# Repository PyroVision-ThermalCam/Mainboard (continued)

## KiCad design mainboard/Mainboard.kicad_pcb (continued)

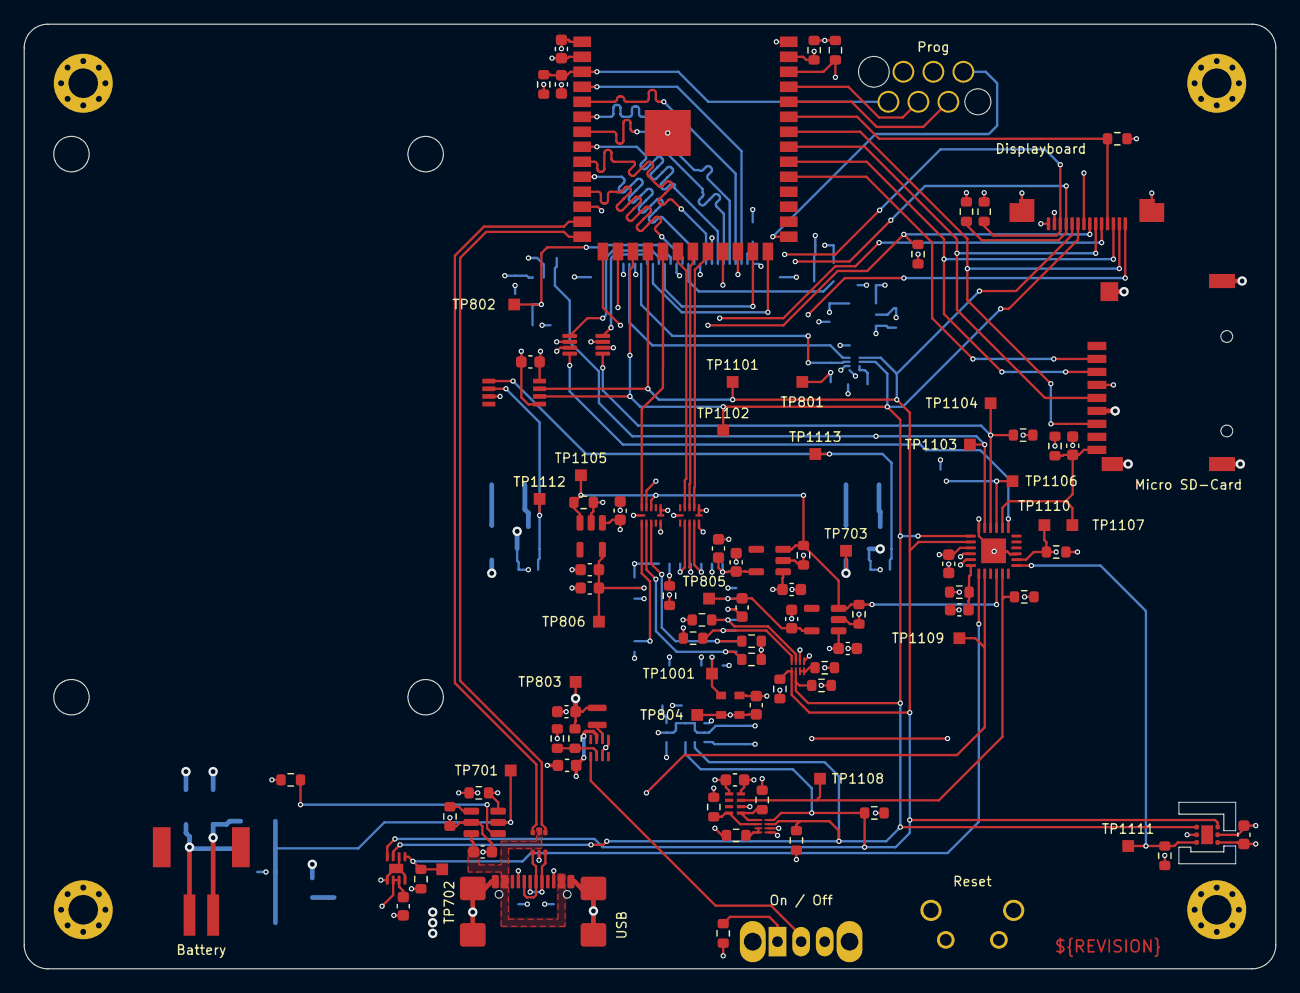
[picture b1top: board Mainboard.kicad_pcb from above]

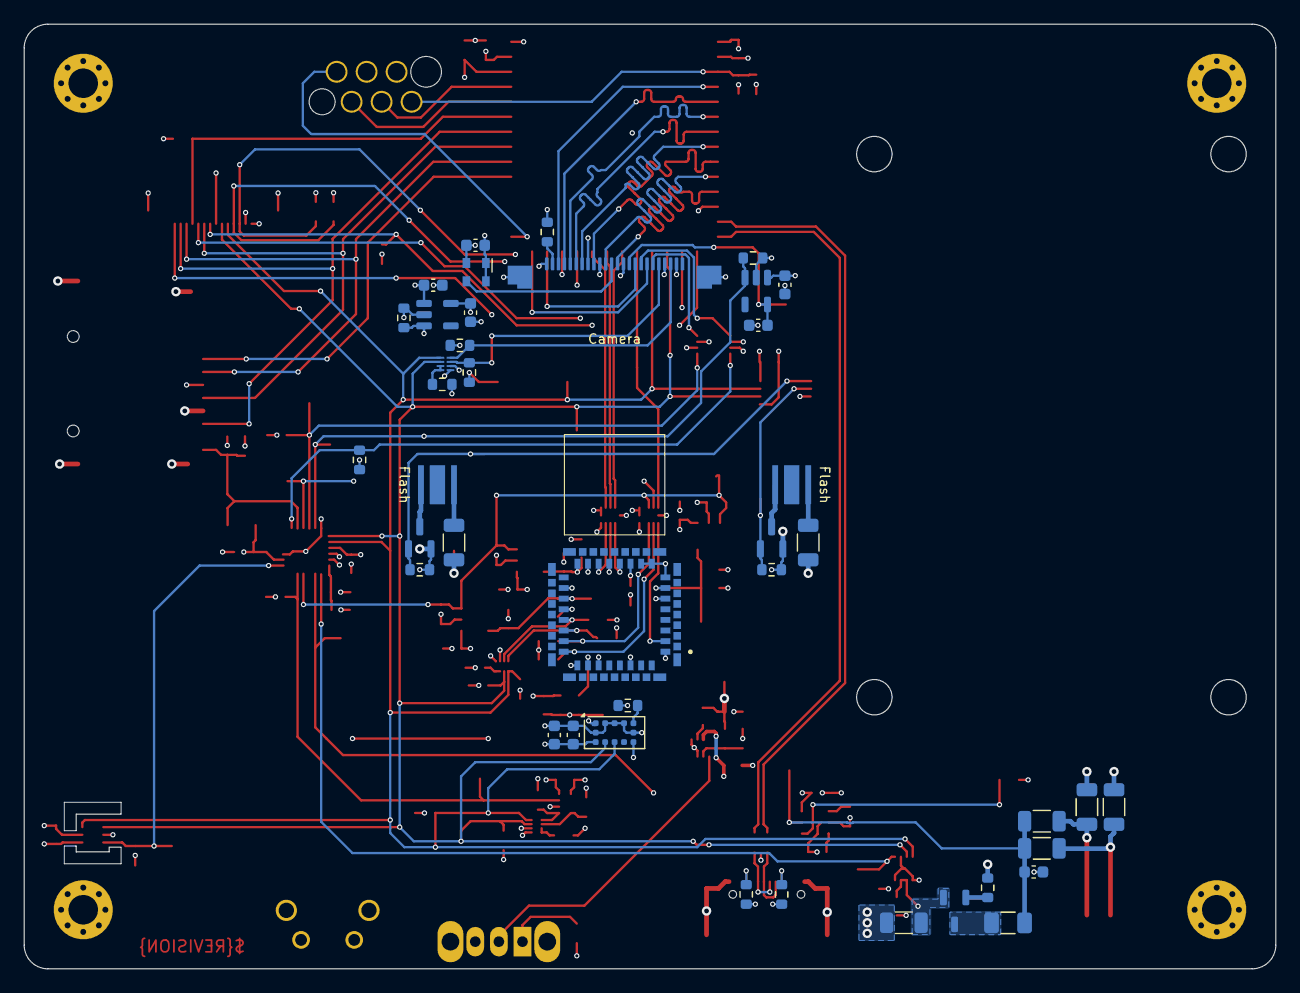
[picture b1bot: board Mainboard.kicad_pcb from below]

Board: 4 copper layers, 106.0 x 80.0 mm, 148 parts (41 on the bottom side), 100 nets.

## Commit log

2026-01-04 Initialize repository
2026-01-04 Initialize branch
2026-01-04 Continue routing, add flash LEDs for the RGB camera, add PWM controller for the Display Backlight and the flash LEDs, add Polyfuse for the battery
2026-01-06 Remove ADC for battery measurement and add a fuel gauge
2026-01-07 New position for display connector
2026-01-07 Replace temperature sensor and optimize the position, replace LiPo battery with a flat one
2026-01-11 Layout complete
2026-01-17 Add reset switch
2026-01-19 Release 1.0.0
2026-01-19 Push outputs from CI/CD (2026-01-19 19:04:05)
2026-01-19 Update CHANGELOG
2026-01-19 Update outputs (release)
2026-01-21 Initialize development branch for version 1.0.1
2026-01-21 Bug: Issue #6
    - Wrong logo path in production data
    Closes: #6
2026-01-21 Task: Issue #7
    - Increase the width of the cutout for the temperature sensor
    - Add missing component informations
    - Fix wrong component informations
    Closes: #7
2026-01-21 Bug: Issue #8
    - Drill drawing is missing
    Closes: #8
2026-01-21 Add feedback from PCBWay
2026-01-21 Release 1.0.1
2026-01-21 Push outputs from CI/CD (2026-01-21 18:28:46)
2026-01-21 Update keep-a-changelog-new-release version to 3
2026-01-22 Initialize development branch for version 1.0.2
2026-01-22 Change PCB color to green / white
2026-02-04 Adjust dimensions
2026-02-04 Bug: Issue #11
    - Add missing name for net for TP701
    Closes: #11
2026-02-05 Feature: Issue #10
    - Replace SD card holder with MSD-4-A
    Closes: #10
2026-02-10 Bug: Fixing several component issues
    Closes: #17
    Closes: #16
    Closes: #15
    Closes: #14
    Closes: #13
    Closes: #12
2026-02-18 Feature: Issue #21
    - Connect the TMP117 temperatur alert pin
    - Add CI/CD workflow to check for changelog updates on pull requests
    Closes #21
2026-02-19 Feature: Issue #18
    - Replace XPGDWT-BS-0000-00Q2E with XPGDWT-BS-0000-00P5E
    - Update CHANGELOG with previous commits
    Closes: #18
2026-02-19 Fix CI/CD
2026-02-23 Add VL53L1X ToF sensor
2026-02-23 Push outputs from CI/CD (2026-02-23 15:32:47)
2026-02-23 Prepare release 1.0.2
2026-02-23 Push outputs from CI/CD (2026-02-23 15:42:33)
2026-02-23 Enhance workflow with concurrency and deployment steps
    Added concurrency and deploy job for GitHub Pages.
2026-02-24 Push outputs from CI/CD (2026-02-24 05:18:54)
2026-02-24 Add documentation badge to README
    Added a badge for documentation in the README.
2026-02-24 Add license badge to README
2026-02-25 Fix wrong datasheet link for the battery connector
2026-03-12 Initialize development branch for revision 1.0.3
2026-04-15 Changed: Fix PCB revision
    Closes: #24
2026-04-15 Changed: Fix different minor assembly ToDos
2026-04-15 Removed: Remove camera PWD signal from camera power supply enable
    - The camera PWD signal is now used as a separate signal
    - Solves incompatible signal levels for both enable pins
    - Fix DRC issues
2026-04-15 Added: Add optional GND connection for camera AF on pin 24
    - Some camera module require a GND connection on this pin
    - CHANGELOG fixes
2026-05-18 Update to KiCad 10
    Closes: #31, #29, #27
2026-05-18 Push outputs from CI/CD (2026-05-18 06:40:41)
